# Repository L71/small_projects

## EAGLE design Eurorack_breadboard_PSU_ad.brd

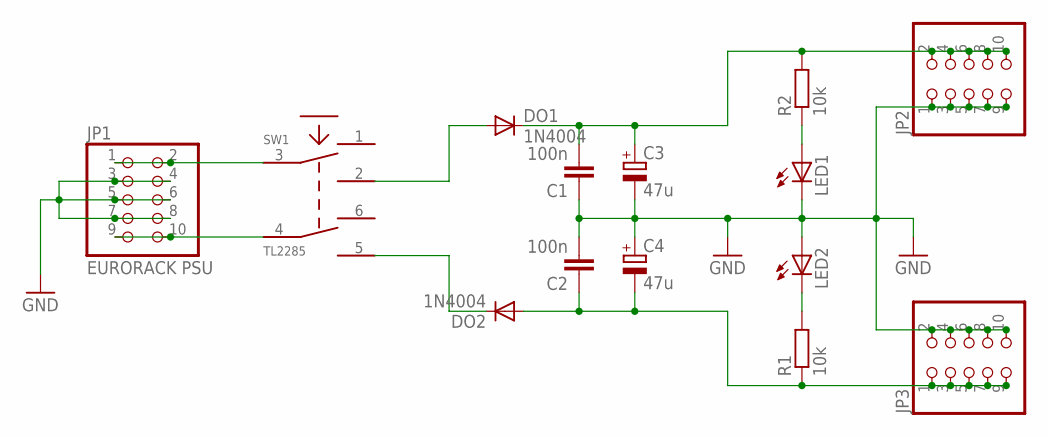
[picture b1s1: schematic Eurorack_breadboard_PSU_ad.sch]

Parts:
C1, C2: 100n; C025-025X050
C3, C4: 47u; E2,5-5
DO1, DO2: 1N4004; DO41-7
JP1: EURORACK PSU; 2X05
JP2, JP3: PINHD-2X5; 2X05
LED1, LED2: LED3MM
R1, R2: 10k; 0207/2V
SW1: TL2285; TL2285_PCB

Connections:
GND: C1.1, C2.2, C3.-, C4.+, JP1.3, JP1.4, JP1.5, JP1.6, JP1.7, JP1.8, JP2.1, JP2.3, JP2.5, JP2.7, JP2.9, JP3.2, JP3.4, JP3.6, JP3.8, JP3.10, LED1.K (C), LED2.A
unnamed: LED1.A, R2.1
unnamed: DO2.C, SW1.5
unnamed: DO1.A, SW1.2
unnamed: LED2.K (C), R1.2
unnamed: JP1.1, JP1.2, SW1.3
unnamed: JP1.9, JP1.10, SW1.4
unnamed: C2.1, C4.-, DO2.A, JP3.1, JP3.3, JP3.5, JP3.7, JP3.9, R1.1
unnamed: C1.2, C3.+, DO1.C, JP2.2, JP2.4, JP2.6, JP2.8, JP2.10, R2.2

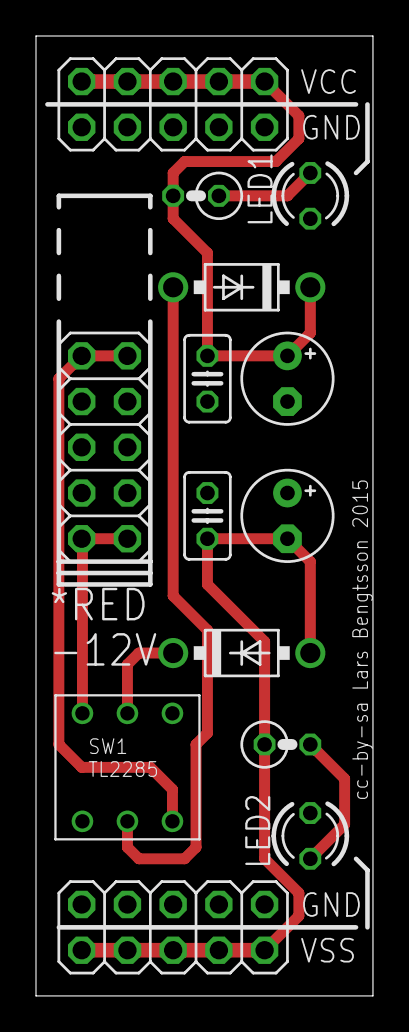
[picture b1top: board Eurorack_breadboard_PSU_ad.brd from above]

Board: 2 copper layers, 18.7 x 53.3 mm, 14 parts (0 on the bottom side), 9 nets.

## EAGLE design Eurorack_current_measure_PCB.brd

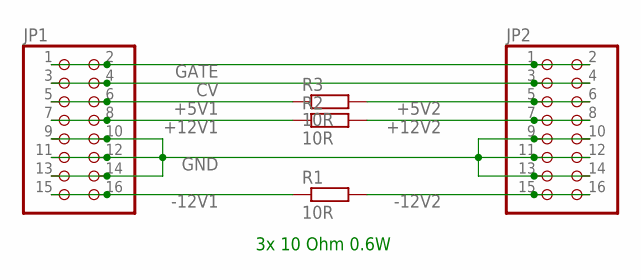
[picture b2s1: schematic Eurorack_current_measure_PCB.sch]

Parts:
JP1, JP2: PINHD-2X8; 2X08
R1, R2, R3: 10R; 0207/10

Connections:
+5V1: JP1.5, JP1.6, R3.1
+5V2: JP2.5, JP2.6, R3.2
+12V1: JP1.7, JP1.8, R2.1
+12V2: JP2.7, JP2.8, R2.2
-12V1: JP1.15, JP1.16, R1.1
-12V2: JP2.15, JP2.16, R1.2
CV: JP1.3, JP1.4, JP2.3, JP2.4
GATE: JP1.1, JP1.2, JP2.1, JP2.2
GND: JP1.9, JP1.10, JP1.11, JP1.12, JP1.13, JP1.14, JP2.9, JP2.10, JP2.11, JP2.12, JP2.13, JP2.14

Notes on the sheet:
3x 10 Ohm 0.6W

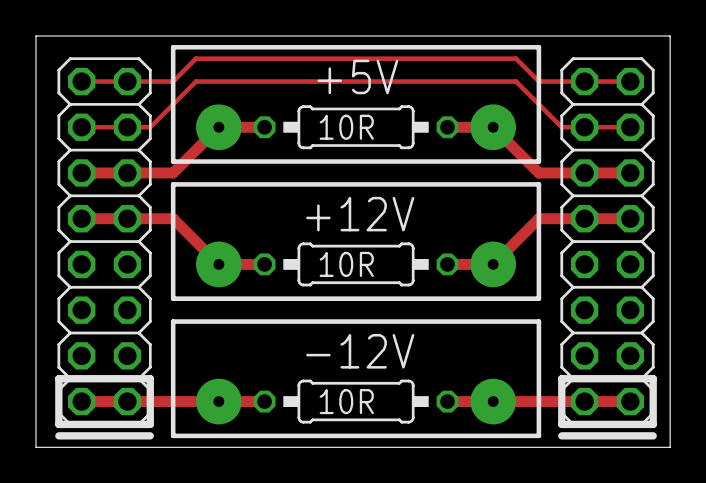
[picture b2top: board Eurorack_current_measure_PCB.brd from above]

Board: 2 copper layers, 35.2 x 22.8 mm, 5 parts (0 on the bottom side), 9 nets.

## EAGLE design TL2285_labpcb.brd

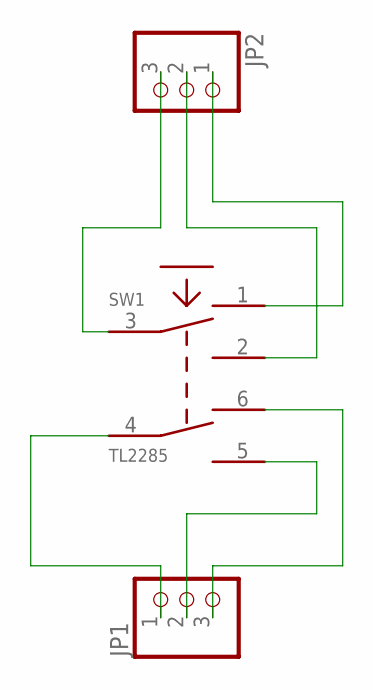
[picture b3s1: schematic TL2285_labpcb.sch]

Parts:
JP1, JP2: PINHD-1X3; 1X03
SW1: TL2285; TL2285_PCB

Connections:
unnamed: JP1.1, SW1.4
unnamed: JP1.2, SW1.5
unnamed: JP1.3, SW1.6
unnamed: JP2.3, SW1.3
unnamed: JP2.1, SW1.1
unnamed: JP2.2, SW1.2

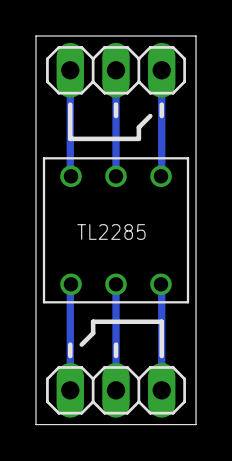
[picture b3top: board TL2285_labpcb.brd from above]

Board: 2 copper layers, 8.9 x 21.6 mm, 3 parts (0 on the bottom side), 6 nets.

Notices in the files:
Eurorack_breadboard_PSU_ad.brd:
cc-by-sa Lars Bengtsson 2015
